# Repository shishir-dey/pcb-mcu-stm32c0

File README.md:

# MCU Card for STM32C031

An STM32C031 microcontroller with M.2 B+M key connector

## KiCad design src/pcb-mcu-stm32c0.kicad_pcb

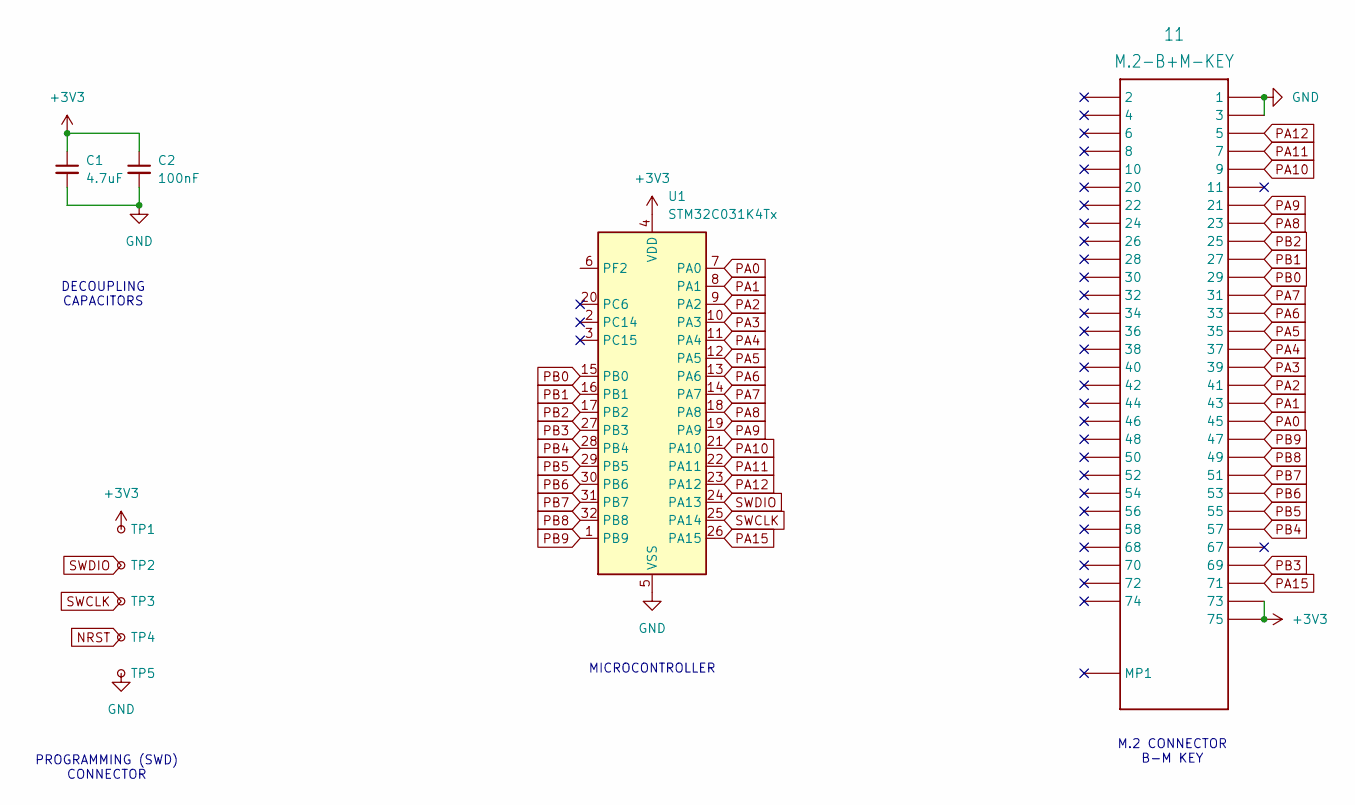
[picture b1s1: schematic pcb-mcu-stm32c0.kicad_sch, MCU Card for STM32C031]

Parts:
11: M.2-B+M-KEY
C1: 4.7uF; C_0603_1608Metric
C2: 100nF; C_0603_1608Metric
TP1, TP2, TP3, TP4, TP5: TestPoint_Small; TestPoint_Pad_D1.0mm
U1: STM32C031K4Tx; LQFP-32_7x7mm_P0.8mm

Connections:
+3V3: 11.P$73 (73), 11.P$75 (75), C1.1, C2.1, TP1.1 (1_1), U1.4 (VDD)
GND: 11.P$1 (1), 11.P$3 (3), C1.2, C2.2, TP5.1 (1_1), U1.5 (VSS)
NRST: TP4.1 (1_1)
PA0: 11.P$45 (45), U1.7 (PA0)
PA1: 11.P$43 (43), U1.8 (PA1)
PA2: 11.P$41 (41), U1.9 (PA2)
PA3: 11.P$39 (39), U1.10 (PA3)
PA4: 11.P$37 (37), U1.11 (PA4)
PA5: 11.P$35 (35), U1.12 (PA5)
PA6: 11.P$33 (33), U1.13 (PA6)
PA7: 11.P$31 (31), U1.14 (PA7)
PA8: 11.P$23 (23), U1.18 (PA8)
PA9: 11.P$21 (21), U1.19 (PA9)
PA10: 11.P$9 (9), U1.21 (PA10)
PA11: 11.P$7 (7), U1.22 (PA11)
PA12: 11.P$5 (5), U1.23 (PA12)
PA15: 11.P$71 (71), U1.26 (PA15)
PB0: 11.P$29 (29), U1.15 (PB0)
PB1: 11.P$27 (27), U1.16 (PB1)
PB2: 11.P$25 (25), U1.17 (PB2)
PB3: 11.P$69 (69), U1.27 (PB3)
PB4: 11.P$57 (57), U1.28 (PB4)
PB5: 11.P$55 (55), U1.29 (PB5)
PB6: 11.P$53 (53), U1.30 (PB6)
PB7: 11.P$51 (51), U1.31 (PB7)
PB8: 11.P$49 (49), U1.32 (PB8)
PB9: 11.P$47 (47), U1.1 (PB9)
SWCLK: TP3.1 (1_1), U1.25 (PA14)
SWDIO: TP2.1 (1_1), U1.24 (PA13)

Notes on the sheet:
M.2 CONNECTOR B-M KEY
MICROCONTROLLER
DECOUPLING CAPACITORS
PROGRAMMING (SWD) CONNECTOR

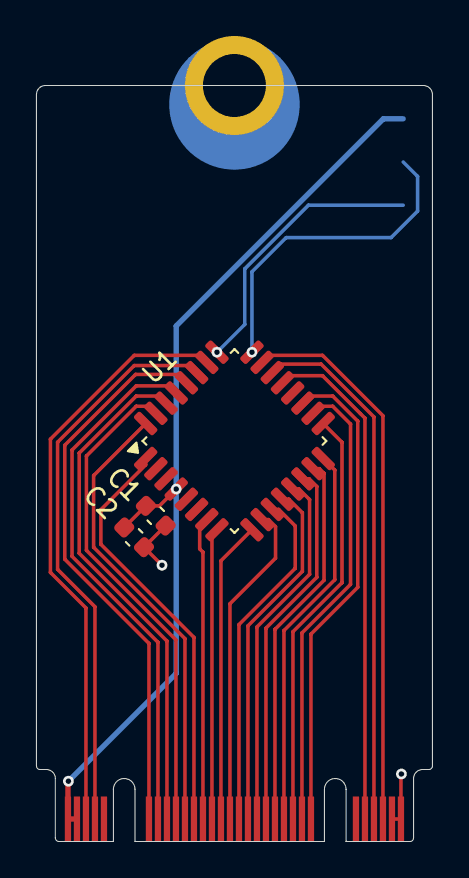
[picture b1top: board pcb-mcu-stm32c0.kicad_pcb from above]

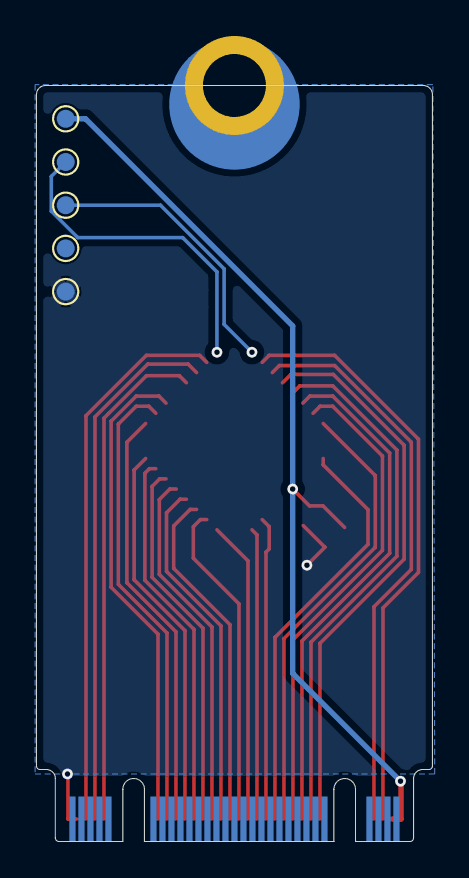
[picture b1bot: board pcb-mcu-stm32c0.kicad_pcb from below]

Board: 2 copper layers, 22.0 x 42.0 mm, 9 parts (5 on the bottom side), 28 nets.

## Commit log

2026-05-09 Add the initial draft of the KiCad design files
